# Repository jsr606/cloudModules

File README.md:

# CLOUD MODULES

## arduino clone with power, serial, I2C and pulses over ethernet
can drive 12V or 5V with mosfet
can switch LCD shutters too
has many LEDs :)

bug warning: 5V and +5V are not connected on PCB, see fix in pics folder

* by [jacob remin](http://www.jacobremin.com) 2018

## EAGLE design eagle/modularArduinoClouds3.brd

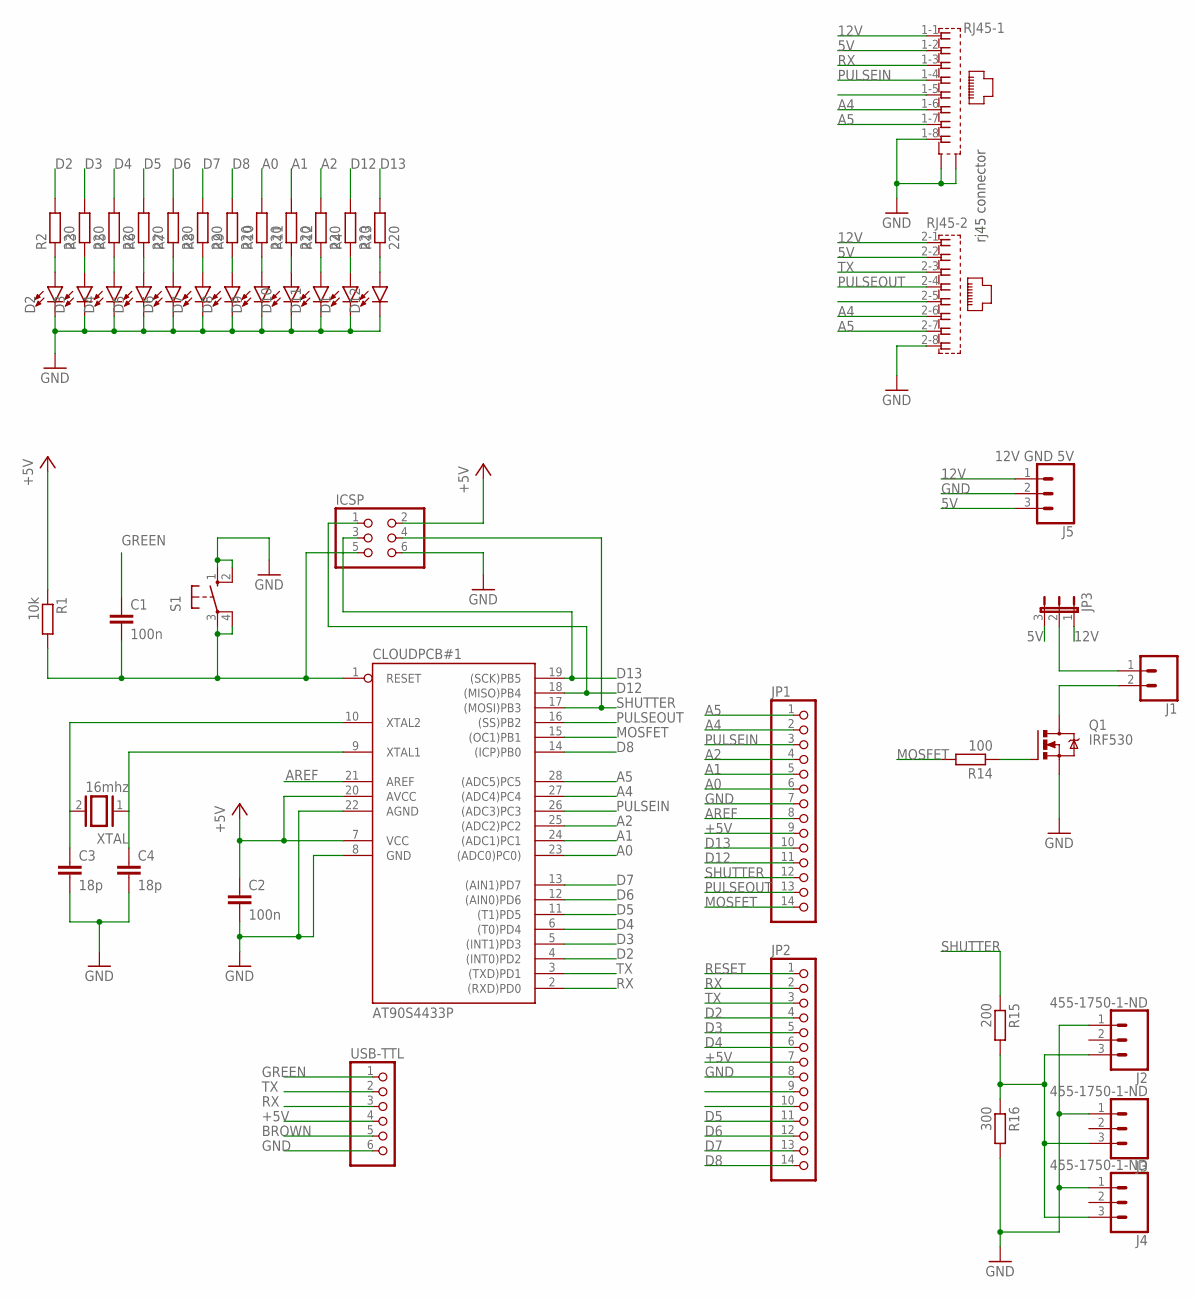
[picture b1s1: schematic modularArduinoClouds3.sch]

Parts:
C1, C2: 100n; C050-025X075
C3, C4: 18p; C050-025X075
CLOUDPCB#1: AT90S4433P; DIL28-3
D1, D2, D3, D4, D5, D6, D7, D8, D9, D10, D11, D12: LED5MM; LED_5MM
ICSP: PINHD-2X3; 2X03
J1: CONN_02; 1X02
J2, J3, J4: 455-1750-1-ND; 1X03
J5: 12V GND 5V; 1X03
JP1, JP2: PINHD-1X14; 1X14
JP3: JP2E; JP2
Q1: IRF530; TO220BV
R1: 10k; 0207/10
R2, R3, R4, R5, R6, R7, R8, R9, R10, R11, R12, R13: 220; 0207/10
R14: 100; 0207/10
R15: 200; 0207/10
R16: 300; 0207/10
RJ45: 557570-1
S1: 10-XX; B3F-10XX
USB-TTL: PINHD-1X6; 1X06
XTAL: 16mhz; QS

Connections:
5V: J5.3, JP3.3, RJ45.1-2 (2), RJ45.2-2 (2)
12V: J5.1, JP3.1, RJ45.1-1 (1), RJ45.2-1 (1)
+5V: C2.1, CLOUDPCB#1.7 (VCC), CLOUDPCB#1.20 (AVCC), ICSP.2, JP1.9, JP2.7, R1.1, USB-TTL.4
A0: CLOUDPCB#1.23 ((ADC0)PC0)), JP1.6, R10.2
A1: CLOUDPCB#1.24 ((ADC1)PC1), JP1.5, R11.2
A2: CLOUDPCB#1.25 ((ADC2)PC2), JP1.4, R12.2
A4: CLOUDPCB#1.27 ((ADC4)PC4), JP1.2, RJ45.1-6 (6), RJ45.2-6 (6)
A5: CLOUDPCB#1.28 ((ADC5)PC5), JP1.1, RJ45.1-7 (7), RJ45.2-7 (7)
AREF: CLOUDPCB#1.21 (AREF), JP1.8
BROWN: USB-TTL.5
D2: CLOUDPCB#1.4 ((INT0)PD2), JP2.4, R2.2
D3: CLOUDPCB#1.5 ((INT1)PD3), JP2.5, R3.2
D4: CLOUDPCB#1.6 ((T0)PD4), JP2.6, R5.2
D5: CLOUDPCB#1.11 ((T1)PD5), JP2.11, R6.2
D6: CLOUDPCB#1.12 ((AIN0)PD6), JP2.12, R7.2
D7: CLOUDPCB#1.13 ((AIN1)PD7), JP2.13, R8.2
D8: CLOUDPCB#1.14 ((ICP)PB0), JP2.14, R9.2
D12: CLOUDPCB#1.18 ((MISO)PB4), ICSP.1, JP1.11, R4.2
D13: CLOUDPCB#1.19 ((SCK)PB5), ICSP.3, JP1.10, R13.2
GND: C2.2, C3.2, C4.2, CLOUDPCB#1.8 (GND), CLOUDPCB#1.22 (AGND), D1.K (C), D2.K (C), D3.K (C), D4.K (C), D5.K (C), D6.K (C), D7.K (C), D8.K (C), D9.K (C), D10.K (C), D11.K (C), D12.K (C), ICSP.6, J2.1, J3.1, J4.1, J5.2, JP1.7, JP2.8, Q1.S, R16.2, RJ45.1-8 (8), RJ45.2-8 (8), RJ45.G1 (S2), RJ45.G3 (S1), S1.1 (S), S1.2 (S1), USB-TTL.6
GREEN: C1.1, USB-TTL.1
MOSFET: CLOUDPCB#1.15 ((OC1)PB1), JP1.14, R14.2
unnamed: D2.A, R2.1
unnamed: D3.A, R3.1
unnamed: C3.1, CLOUDPCB#1.10 (XTAL2), XTAL.2
unnamed: C4.1, CLOUDPCB#1.9 (XTAL1), XTAL.1
unnamed: J1.2, Q1.D
unnamed: D4.A, R5.1
unnamed: D5.A, R6.1
unnamed: D6.A, R7.1
unnamed: D7.A, R8.1
unnamed: D8.A, R9.1
unnamed: D9.A, R10.1
unnamed: D10.A, R11.1
unnamed: D11.A, R12.1
unnamed: Q1.G, R14.1
unnamed: J1.1, JP3.2
unnamed: J2.3, J3.3, J4.3, R15.2, R16.1
unnamed: D1.A, R4.1
unnamed: D12.A, R13.1
PULSEIN: CLOUDPCB#1.26 ((ADC3)PC3), JP1.3, RJ45.1-4 (4)
PULSEOUT: CLOUDPCB#1.16 ((SS)PB2), JP1.13, RJ45.2-4 (4)
RESET: C1.2, CLOUDPCB#1.1 (RESET), ICSP.5, JP2.1, R1.2, S1.3, S1.4 (P1)
RX: CLOUDPCB#1.2 ((RXD)PD0), JP2.2, RJ45.1-3 (3), USB-TTL.3
SHUTTER: CLOUDPCB#1.17 ((MOSI)PB3), ICSP.4, JP1.12, R15.1
TX: CLOUDPCB#1.3 ((TXD)PD1), JP2.3, RJ45.2-3 (3), USB-TTL.2

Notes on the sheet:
rj45 connector

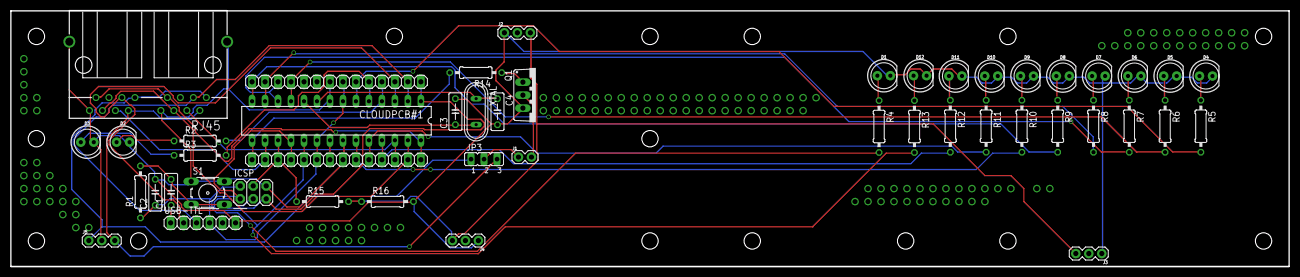
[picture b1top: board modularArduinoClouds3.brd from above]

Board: 2 copper layers, 250.0 x 50.0 mm, 47 parts (0 on the bottom side), 45 nets.

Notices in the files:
parts and their libraries:
SparkFun-Connectors: Licensing: Creative Commons ShareAlike 4.0 International - https://creativecommons.org/licenses/by-sa/4.0
